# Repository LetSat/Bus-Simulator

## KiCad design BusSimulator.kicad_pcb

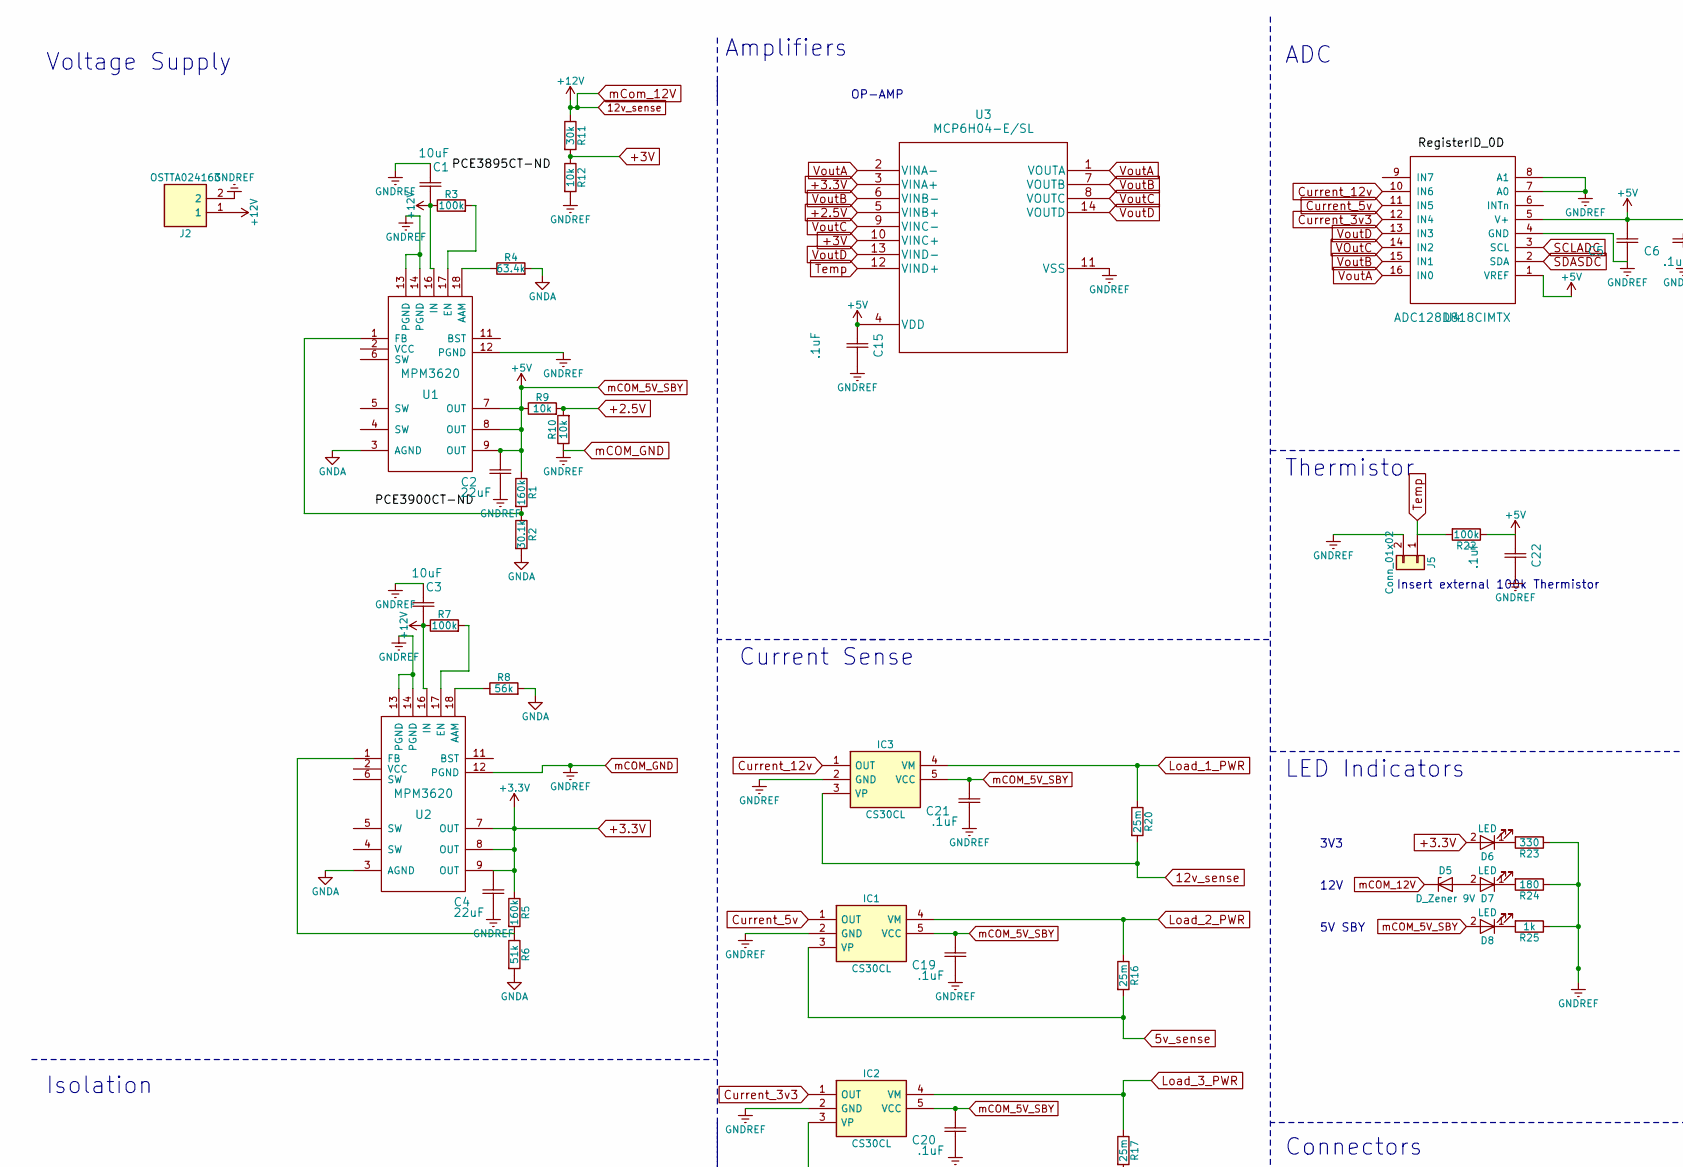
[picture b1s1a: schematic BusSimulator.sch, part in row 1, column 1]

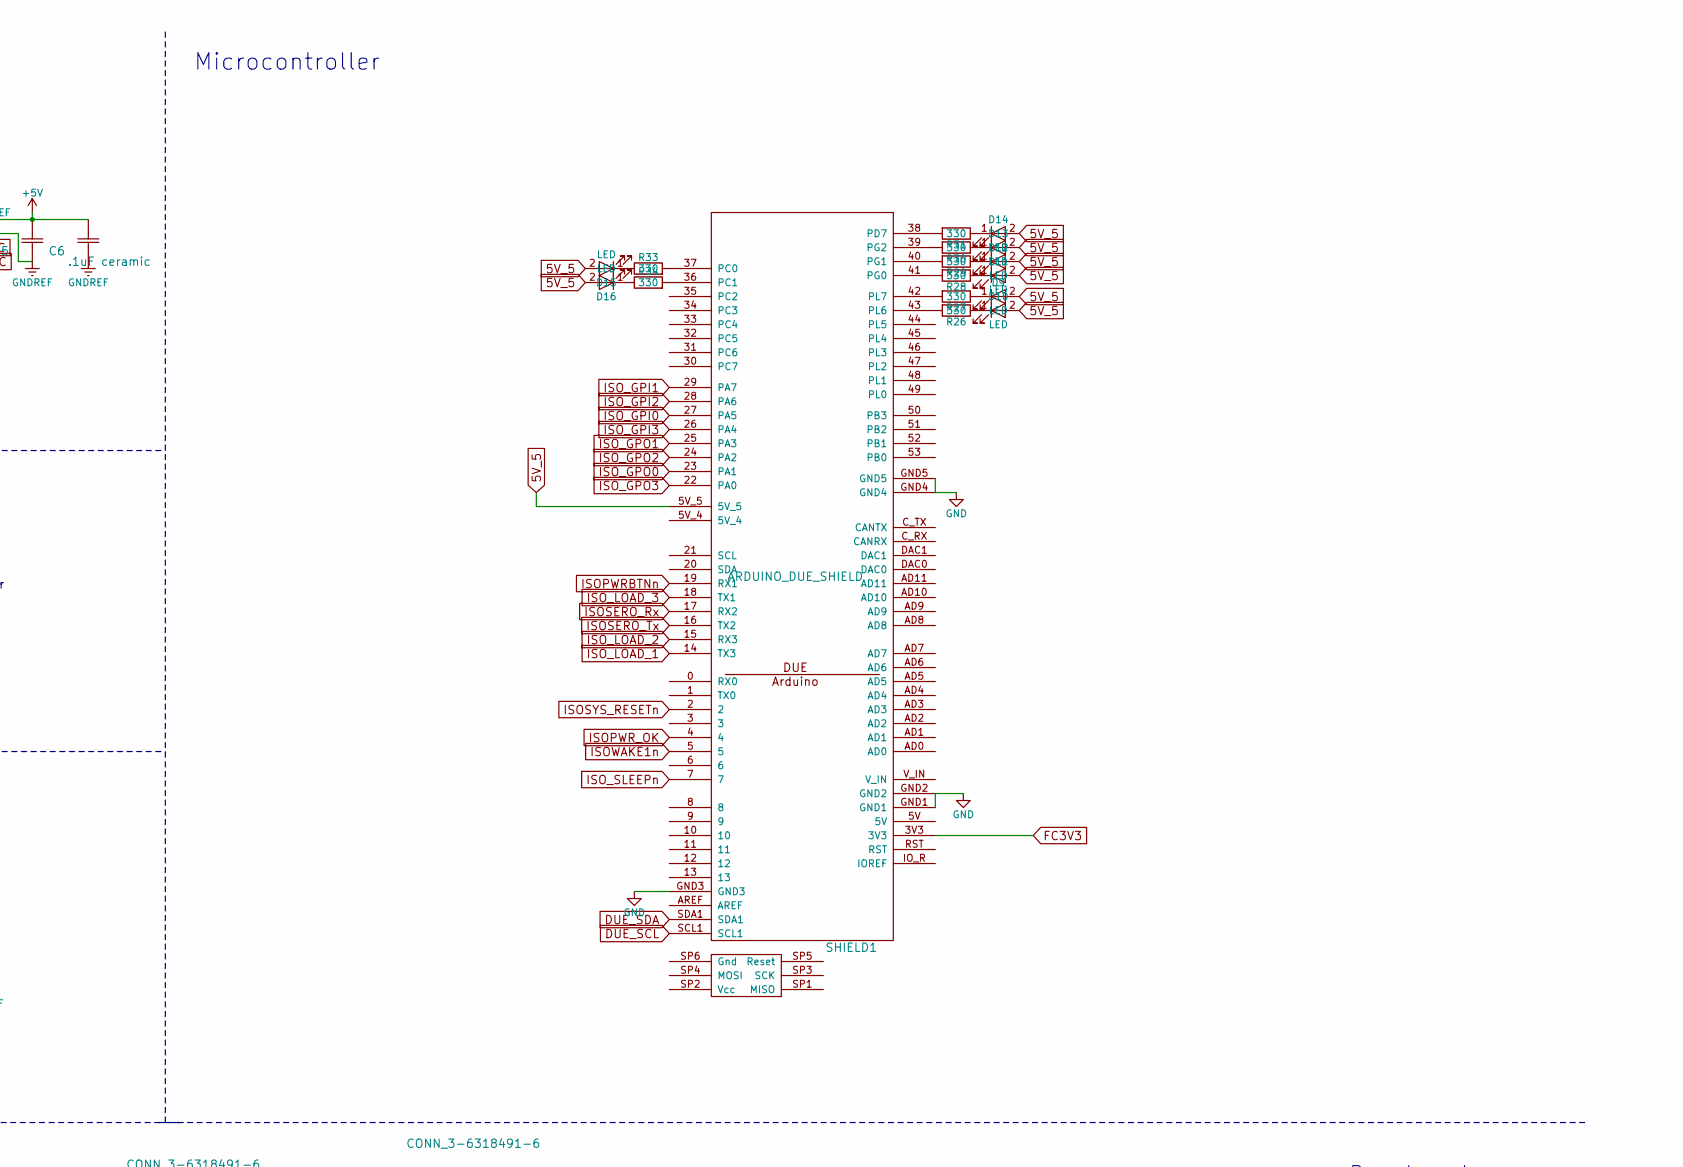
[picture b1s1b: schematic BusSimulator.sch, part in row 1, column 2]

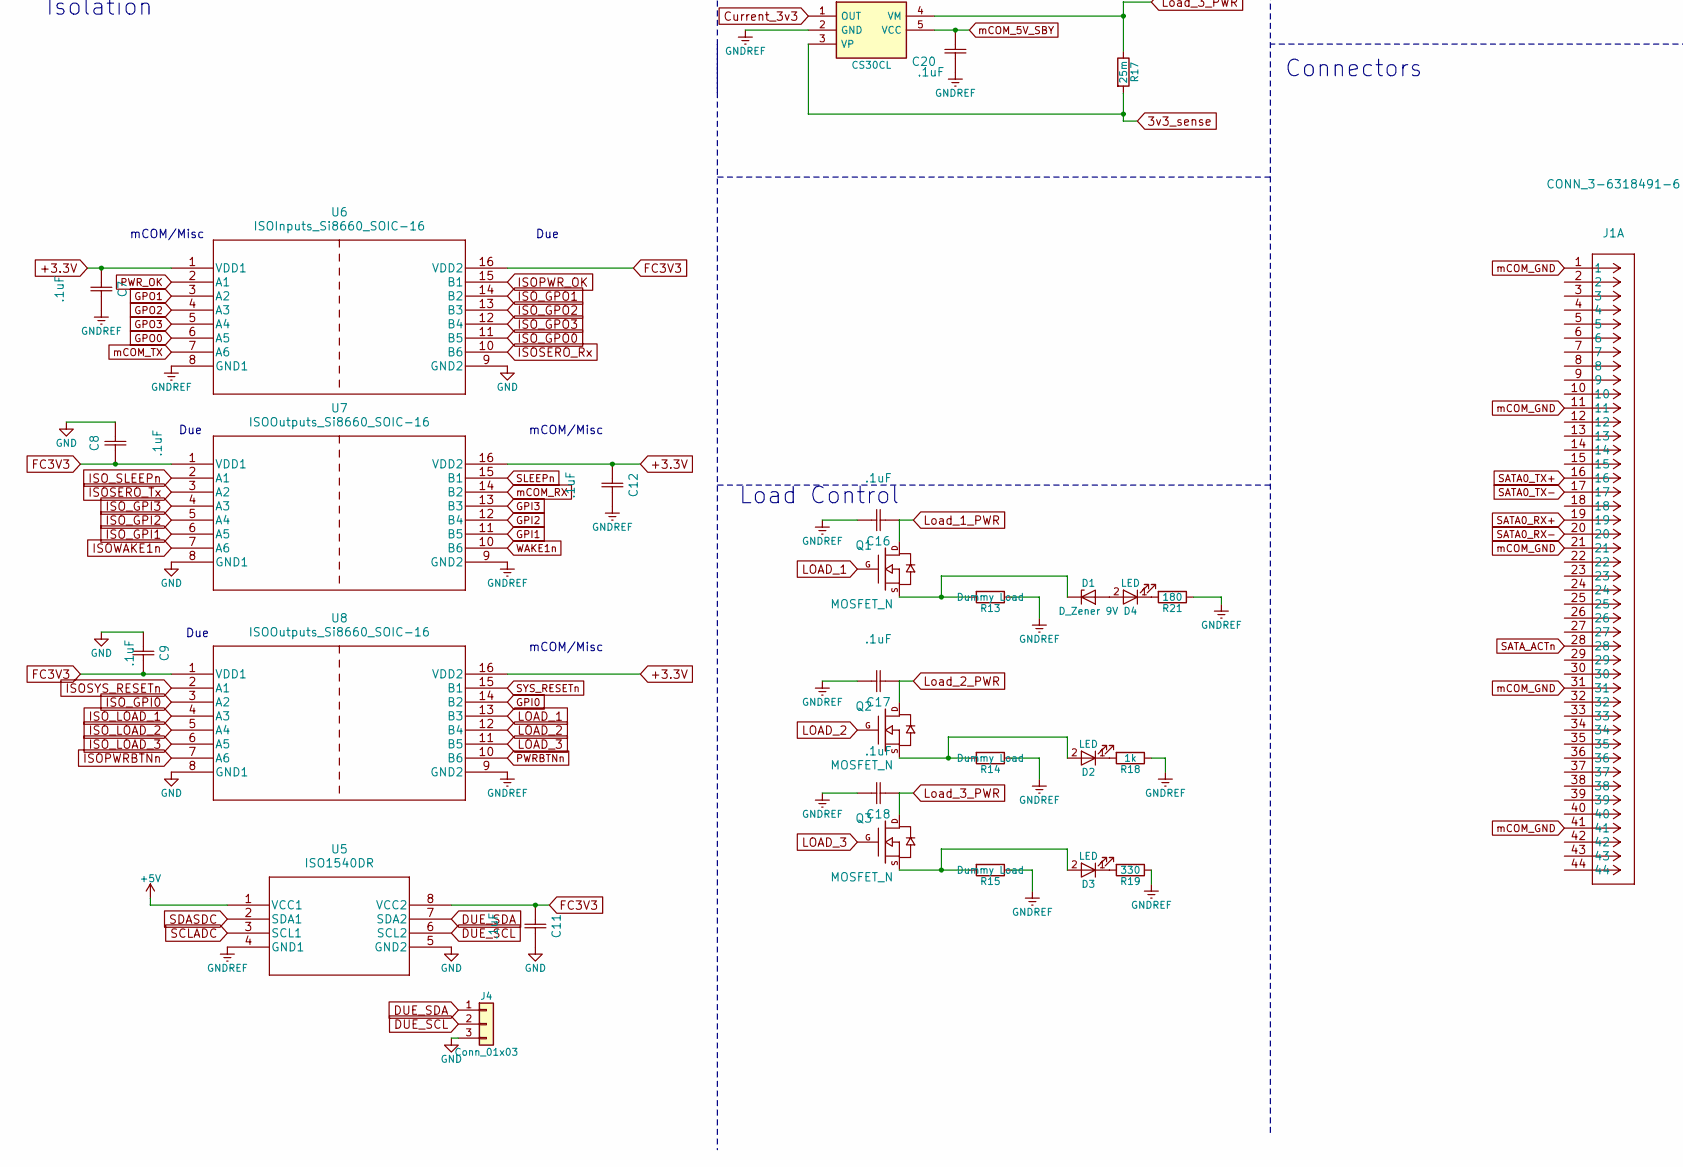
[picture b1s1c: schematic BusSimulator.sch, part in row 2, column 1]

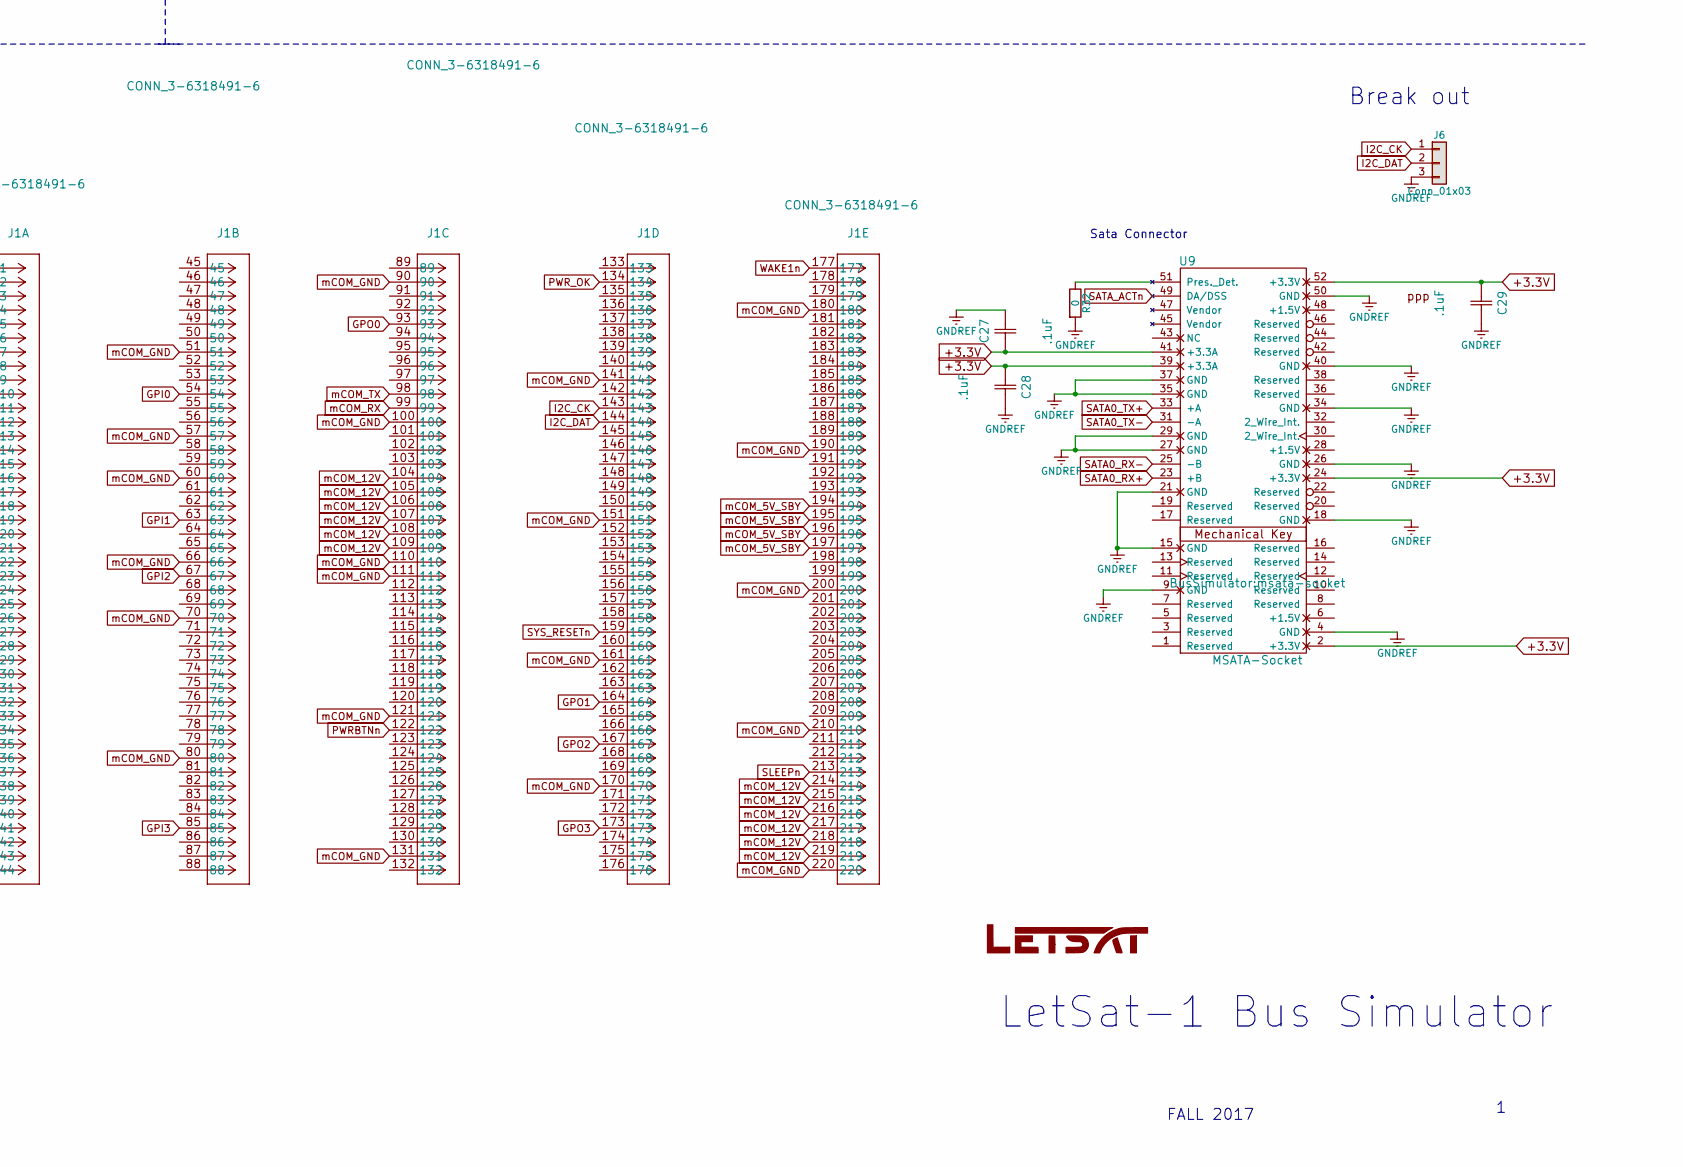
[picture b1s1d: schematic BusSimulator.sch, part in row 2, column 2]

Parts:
C1, C3: 10uF; C22
C2, C4: 22uF; C22
C5: 1uF Electrolytic; C22
C6: .1uF ceramic; C22
C7, C8, C9, C11, C12, C15, C16, C17, C18, C19, C20, C21, C22, C27, C28, C29: .1uF; C_0603
D1, D5: D_Zener 9V; D_SOD-323
D2, D3, D4, D6, D7, D8, D9, D10, D11, D12, D13, D14, D15, D16: LED; D_1206
G1: LOGO; LetSatLogo440
IC1, IC2, IC3: CS30CL; SOT95P280X145-5N; Manufacturer_Part_Number CS30CL
J1: CONN_3-6318491-6; ComExpressMini10
J2: OSTTA024163; Manufacturer_Part_Number OSTTA024163
J4, J6: Conn_01x03; Pin_Header_Straight_1x03_Pitch2.54mm
J5: Conn_01x02; Pin_Header_Straight_1x02_Pitch2.54mm
Q1, Q2, Q3: MOSFET_N; SOT-23
R1, R5: 160k; R_0805
R2: 30.1k; R_0805
R3, R7: 100k; R_0805
R4: 63.4k; R_0805
R6: 51k; R_0805
R8: 56k; R_0805
R9, R10, R12: 10k; R_0603
R11: 30k; R_0603
R13, R14, R15: Dummy Load; R_2512
R16, R17, R20: 25m; R_0805
R18, R25: 1k; R_0603
R19, R23, R26, R27, R28, R29, R30, R31, R33, R34: 330; R_0603
R21, R24: 180; R_0603
R22: 100k; R_0603
R32: 0; R_0805
SHIELD1: ARDUINO_DUE_SHIELD; Arduino_Due_Shield
U1, U2: MPM3620; QFN-20
U3: MCP6H04-E/SL; MCP6H04-E
U4: ADC128D818CIMTX
U5: ISO1540DR
U6: ISOInputs_Si8660_SOIC-16; SI8660BA-B-IS1
U7, U8: ISOOutputs_Si8660_SOIC-16; SI8660BA-B-IS1
U9: MSATA-Socket; msata-socket

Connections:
3v3_sense: IC2.3 (VP), R17.2
5V_5: D9.2 (A), D10.2 (A), D11.2 (A), D12.2 (A), D13.2 (A), D14.2 (A), D15.2 (A), D16.2 (A), SHIELD1.5V_5
5v_sense: IC1.3 (VP), R16.2
12v_sense: C1.2, C3.2, D5.1 (K), IC3.3 (VP), J1.104, J1.105, J1.106, J1.107, J1.108, J1.109, J1.214, J1.215, J1.216, J1.217, J1.218, J1.219, J2.1, R3.1, R7.1, R11.1, R20.2, U1.16 (IN), U2.16 (IN)
+2.5V: R9.2, R10.2, U3.5 (VINB+)
+3.3V: C4.2, C7.1, C12.1, C27.1, C28.1, C29.1, D6.2 (A), R5.1, U2.7 (OUT), U2.8 (OUT), U2.9 (OUT), U3.3 (VINA+), U6.1 (VDD1), U7.16 (VDD2), U8.16 (VDD2), U9.2 (+3.3V), U9.24 (+3.3V), U9.39 (+3.3A), U9.41 (+3.3A), U9.52 (+3.3V)
+3V: R11.2, R12.1, U3.10 (VINC+)
Current_3v3: IC2.1 (OUT), U4.12 (IN4)
Current_5v: IC1.1 (OUT), U4.11 (IN5)
Current_12v: IC3.1 (OUT), U4.10 (IN6)
DUE_SCL: J4.2, SHIELD1.SCL1, U5.6 (SCL2)
DUE_SDA: J4.1, SHIELD1.SDA1, U5.7 (SDA2)
FC3V3: C8.1, C9.2, C11.1, SHIELD1.3V3, U5.8 (VCC2), U6.16 (VDD2), U7.1 (VDD1), U8.1 (VDD1)
GND: C8.2, C9.1, C11.2, J4.3, SHIELD1.GND1, SHIELD1.GND2, SHIELD1.GND3, SHIELD1.GND4, SHIELD1.GND5, U5.5 (GND2), U6.9 (GND2), U7.8 (GND1), U8.8 (GND1)
GNDA: R2.2, R4.2, R6.2, R8.2, U1.3 (AGND), U2.3 (AGND)
GPI0: J1.54, U8.14 (B2)
GPI1: J1.63, U7.11 (B5)
GPI2: J1.67, U7.12 (B4)
GPI3: J1.85, U7.13 (B3)
GPO0: J1.93, U6.6 (A5)
GPO1: J1.164, U6.3 (A2)
GPO2: J1.167, U6.4 (A3)
GPO3: J1.173, U6.5 (A4)
I2C_CK: J1.143, J6.1
I2C_DAT: J1.144, J6.2
ISOPWRBTNn: SHIELD1.19 (RX1), U8.7 (A6)
ISOPWR_OK: SHIELD1.4, U6.15 (B1)
ISOSERO_Rx: SHIELD1.17 (RX2), U6.10 (B6)
ISOSERO_Tx: SHIELD1.16 (TX2), U7.3 (A2)
ISOSYS_RESETn: SHIELD1.2, U8.2 (A1)
ISOWAKE1n: SHIELD1.5, U7.7 (A6)
ISO_GPI0: SHIELD1.27 (PA5), U8.3 (A2)
ISO_GPI1: SHIELD1.29 (PA7), U7.6 (A5)
ISO_GPI2: SHIELD1.28 (PA6), U7.5 (A4)
ISO_GPI3: SHIELD1.26 (PA4), U7.4 (A3)
ISO_GPO0: SHIELD1.23 (PA1), U6.11 (B5)
ISO_GPO1: SHIELD1.25 (PA3), U6.14 (B2)
ISO_GPO2: SHIELD1.24 (PA2), U6.13 (B3)
ISO_GPO3: SHIELD1.22 (PA0), U6.12 (B4)
ISO_LOAD_1: SHIELD1.14 (TX3), U8.4 (A3)
ISO_LOAD_2: SHIELD1.15 (RX3), U8.5 (A4)
ISO_LOAD_3: SHIELD1.18 (TX1), U8.6 (A5)
ISO_SLEEPn: SHIELD1.7, U7.2 (A1)
LOAD_1: Q1.G, U8.13 (B3)
LOAD_2: Q2.G, U8.12 (B4)
LOAD_3: Q3.G, U8.11 (B5)
Load_1_PWR: C16.1, IC3.4 (VM), Q1.D, R20.1
Load_2_PWR: C17.1, IC1.4 (VM), Q2.D, R16.1
Load_3_PWR: C18.1, IC2.4 (VM), Q3.D, R17.1
unnamed: D1.1 (K), Q1.S, R13.2
unnamed: D1.2 (A), D4.2 (A)
unnamed: D2.1 (K), R18.2
unnamed: D2.2 (A), Q2.S, R14.2
unnamed: D3.1 (K), R19.2
unnamed: D3.2 (A), Q3.S, R15.2
unnamed: D4.1 (K), R21.2
unnamed: D5.2 (A), D7.2 (A)
unnamed: D6.1 (K), R23.2
unnamed: D7.1 (K), R24.2
unnamed: D8.1 (K), R25.2
unnamed: D9.1 (K), R27.1
unnamed: D10.1 (K), R26.1
unnamed: D11.1 (K), R28.1
unnamed: D12.1 (K), R29.1
unnamed: D13.1 (K), R30.1
unnamed: D14.1 (K), R31.1
unnamed: D15.1 (K), R33.1
unnamed: D16.1 (K), R34.1
unnamed: R1.2, R2.1, U1.1 (FB)
unnamed: R3.2, U1.17 (EN)
unnamed: R4.1, U1.18 (AAM)
unnamed: R5.2, R6.1, U2.1 (FB)
unnamed: R7.2, U2.17 (EN)
unnamed: R8.1, U2.18 (AAM)
unnamed: R26.2, SHIELD1.43 (PL6)
unnamed: R27.2, SHIELD1.42 (PL7)
unnamed: R28.2, SHIELD1.41 (PG0)
unnamed: R29.2, SHIELD1.40 (PG1)
unnamed: R30.2, SHIELD1.39 (PG2)
unnamed: R31.2, SHIELD1.38 (PD7)
unnamed: R32.1, U9.51 (Pres._Det.)
unnamed: R33.2, SHIELD1.37 (PC0)
unnamed: R34.2, SHIELD1.36 (PC1)
PWRBTNn: J1.122, U8.10 (B6)
PWR_OK: J1.134, U6.2 (A1)
SATA0_RX+: J1.19, U9.23 (+B)
SATA0_RX-: J1.20, U9.25 (-B)
SATA0_TX+: J1.16, U9.33 (+A)
SATA0_TX-: J1.17, U9.31 (-A)
SATA_ACTn: J1.28, U9.49 (DA/DSS)
SCLADC: U4.3 (SCL), U5.3 (SCL1)
SDASDC: U4.2 (SDA), U5.2 (SDA1)
SLEEPn: J1.213, U7.15 (B1)
SYS_RESETn: J1.159, U8.15 (B1)
Temp: J5.1, R22.2, U3.12 (VIND+)
VOutC: U3.8 (VOUTC), U3.9 (VINC-), U4.14 (IN2)
VoutA: U3.1 (VOUTA), U3.2 (VINA-), U4.16 (IN0)
VoutB: U3.6 (VINB-), U3.7 (VOUTB), U4.15 (IN1)
VoutD: U3.13 (VIND-), U3.14 (VOUTD), U4.13 (IN3)
WAKE1n: J1.177, U7.10 (B6)
mCOM_5V_SBY: C2.2, C5.2, C6.2, C15.1, C19.2, C20.2, C21.2, C22.1, D8.2 (A), IC1.5 (VCC), IC2.5 (VCC), IC3.5 (VCC), J1.194, J1.195, J1.196, J1.197, R1.1, R9.1, R22.1, U1.7 (OUT), U1.8 (OUT), U1.9 (OUT), U3.4 (VDD), U4.1 (VREF), U4.5 (V+), U5.1 (VCC1)
mCOM_GND: C1.1, C2.1, C3.1, C4.1, C5.1, C6.1, C7.2, C12.2, C15.2, C16.2, C17.2, C18.2, C19.1, C20.1, C21.1, C22.2, C27.2, C28.2, C29.2, IC1.2 (GND), IC2.2 (GND), IC3.2 (GND), J1.1, J1.11, J1.21, J1.31, J1.41, J1.51, J1.57, J1.60, J1.66, J1.70, J1.80, J1.90, J1.100, J1.110, J1.111, J1.121, J1.131, J1.141, J1.151, J1.161, J1.170, J1.180, J1.190, J1.200, J1.210, J1.220, J1.TAB1, J1.TAB2, J2.2, J5.2, J6.3, R10.1, R12.2, R13.1, R14.1, R15.1, R18.1, R19.1, R21.1, R23.1, R24.1, R25.1, R32.2, U1.12 (PGND), U1.13 (PGND), U1.14 (PGND), U2.12 (PGND), U2.13 (PGND), U2.14 (PGND), U3.11 (VSS), U4.4 (GND), U4.7 (A0), U4.8 (A1), U5.4 (GND1), U6.8 (GND1), U7.9 (GND2), U8.9 (GND2), U9.4 (GND), U9.9 (GND), U9.15 (GND), U9.18 (GND), U9.21 (GND), U9.26 (GND), U9.27 (GND), U9.29 (GND), U9.34 (GND), U9.35 (GND), U9.37 (GND), U9.40 (GND), U9.50 (GND)
mCOM_RX: J1.99, U7.14 (B2)
mCOM_TX: J1.98, U6.7 (A6)

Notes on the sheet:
Break out
Isolation
LED Indicators
OP-AMP
ADC
3V3
12V
5V SBY
Voltage Supply
Amplifiers
Microcontroller
Connectors
LetSat-1 Bus Simulator
FALL 2017
Current Sense
Load Control
Thermistor
Insert external 100k Thermistor
Sata Connector
Due
mCOM/Misc

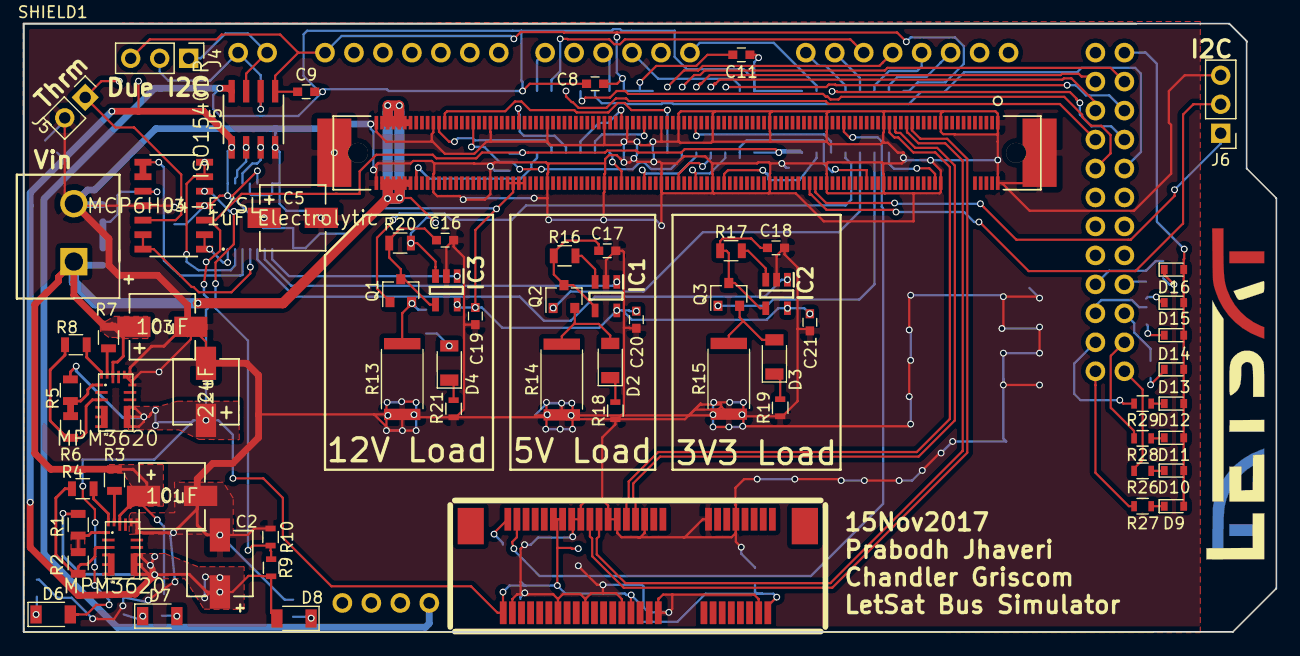
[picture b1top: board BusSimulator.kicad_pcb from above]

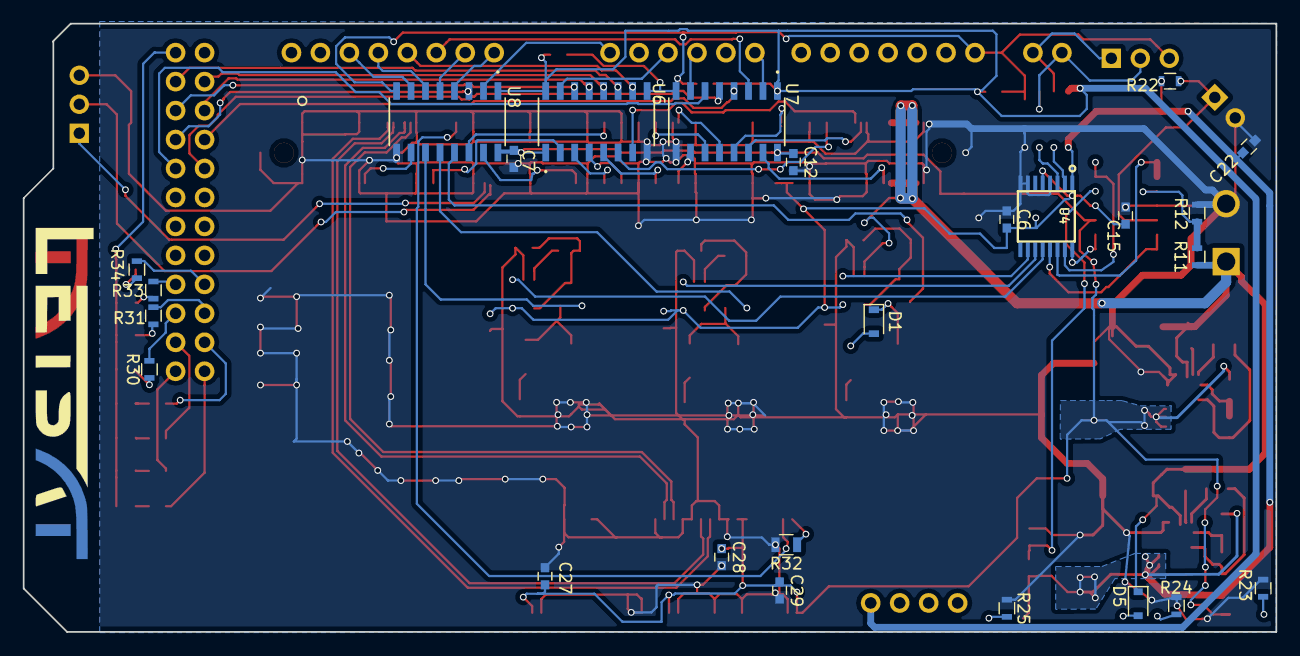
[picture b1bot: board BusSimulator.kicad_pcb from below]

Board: 2 copper layers, 109.9 x 53.3 mm, 95 parts (26 on the bottom side), 104 nets.

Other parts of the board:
G1#2: LOGO; LetSatLogo440

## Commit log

2017-11-01 Project Skeleton
2017-11-01 i started
2017-11-02 started 1 boost conv
2017-11-02 Finished 3v3 and 5V
2017-11-08 MSATA Connector Added
    David Trost, Keishaun Mcmillian
2017-11-09 Receptacle for COM Module Footprint
2017-11-09 Add op amp footprint
2017-11-09 Add com express export
2017-11-09 moved pads to bus sim library
2017-11-09 added dc connector and outline pcb
2017-11-09 Add mCOM connector to library and schematic
2017-11-09 dc jack
2017-11-09 POWER SUPPLY STUFF
2017-11-09 Clean up, add logo
2017-11-09 CONNECTOR MAPPED
2017-11-09 Add ADC symbol
2017-11-09 Add ADC pcb footprint
2017-11-09 Add symbols for 666 isolator
2017-11-09 schematic build voltage sense
2017-11-09 Add I2C isolator symbols
2017-11-09 opamp stuff
2017-11-09 Add logo footprint
2017-11-09 ADDED LOGO
2017-11-09 Make test change
2017-11-09 added 6 channel iso and 12v to mcom
2017-11-09 pcb oppto iso
2017-11-09 Revert "ADDED LOGO"
    This reverts commit 0039451504e15c76ab54593e9d3a51ab69c632c3.
2017-11-09 Reverting
2017-11-09 add logo test
2017-11-09 Add isloator
2017-11-09 Remove dust
2017-11-09 logo
2017-11-09 Correct COM Express net names
2017-11-10 fixed connector for mcom
2017-11-11 removed unsed pins
2017-11-11 pullled pins to isolate
2017-11-11 Schematic work
2017-11-12 Finished schematic (not verifed)
2017-11-12 Correct some thangs
2017-11-12 pushed components on the pcb
2017-11-13 Fixed mosfetts
2017-11-13 started pcb
2017-11-13 Revert failed merge
2017-11-13 Fix mosfets
2017-11-14 Correct some issues with isolation pin mappings
2017-11-14 Fix some more isolator errors
2017-11-14 Organize isolator nets and arrange PCB components
2017-11-14 Organize Due-to-isolator connection
2017-11-14 Routed mCOM connector and isolators
2017-11-14 added leds
2017-11-14 zoning fix
2017-11-14 Fix fill nets
2017-11-14 fix outline
2017-11-14 Fix edge cut
2017-11-14 finished leds
2017-11-14 Mostly finished
2017-11-14 Do the boring part, prabodh
2017-11-14 Pass DRC
2017-11-14 fix clreance
2017-11-14 Fix silkscreens and ground planes
2017-11-14 Prepare for OSHPark
2017-11-14 Improve ground planes, add tabs to mCOM connector
2017-11-14 Add solidworks model
2017-11-14 Correct solidworks model
2017-11-15 Fix a couple critical errors
2017-11-15 Fix more planing errors, pass DRC
2017-11-15 Silk text to mask
2017-11-15 Perfectionism
2017-11-15 Switch back to silkscreen

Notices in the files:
parts and their libraries:
Copyright 2016 Accelerated Designs. All rights reserved.
